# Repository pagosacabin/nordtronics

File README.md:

# Nordtronics

Code, hardware designs, and CAD models from **Nordtronics** (Pagosa Springs, CO) —
an off-grid solar, battery, and IoT practice. Custom LiFePO4 battery builds,
off-grid solar installs, and wireless sensor systems (ESP32 / LoRa / MQTT /
Home Assistant).

## Layout

- `backend/` — wildfire pipeline: Mosquitto broker, ingest worker, read-only
  FastAPI service, and the deployment guide (`DEPLOY.md`).
- `firmware/wildfire-node-v1/` — unified LoRa wildfire node/base-station
  firmware (Heltec LoRa 32 V4).
- `android/companion-v0/` — Android companion app for the wildfire network.
- `website/` — nordtronics.io site.
- `docs/` — runbooks and design docs (`docs/wildfire/` for the wildfire net).
- `firmware/cistern-monitor/` — Tank-Monitor remote cistern level monitor:
  ESP32-S3 + SX1262 LoRa TX/RX pair, ultrasonic level sensing, MQTT/Home
  Assistant integration (`cistern_unified.ino`).
- `firmware/lora-display/` — LoRa radio experiments on Heltec LoRa V3 boards,
  including display and RF-preset sketches.
- `python/ultrasonic-sensors/` — MicroPython scripts for ultrasonic distance
  sensing with OLED/LCD output.
- `hardware/battery-pcb/` — KiCad project archives for the custom main battery
  PCB (JK BMS based LiFePO4 pack), including versioned iterations.
- `hardware/busbar/` — Busbar designs for EVE 280Ah cells.
- `cad/first-project/` — Early KiCad project archives.
- `cad/robotic-arm/` — Robotic arm 3D model (STEP).

Archived `.zip` files are kept as-is, preserving the original design history.
- `installs/solar/` — Off-grid solar + storage install notes.

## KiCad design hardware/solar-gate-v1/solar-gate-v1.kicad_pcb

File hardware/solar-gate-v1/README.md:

# solar-gate-v1 — solar cold-charge gate (EDA flow test vehicle)

**TEST BOARD ONLY. Not production, not reviewed, no Gerbers, no fab output.**

This project exists to cold-test the schematic → layout → autoroute rung of the
toolchain against a real circuit. The circuit itself is the approved solar
cold-charge gate spec, but nothing here has been bench-validated and nothing
should be built from it until Stephen has reviewed both the schematic and the
layout.

## Circuit

Warm → NTC low → `VA < VTH` → comparator output pulls `GATE` low → Q1 on.
Cold / no sun → `GATE` floats to `Panel+` through Rg → Q1 off.

| Ref | Part | Package | Notes |
|-----|------|---------|-------|
| Q1  | AO3401 (P-ch MOSFET) | SOT-23 | 1=G, 2=S, 3=D |
| U1  | TLV3401 (nanopower comparator, open-drain) | **SOT-23-5** | see pinout note below |
| D1  | TL431 (2.5 V shunt reference) | SOT-23-3 | 1=K, 2=REF, 3=A (TI DBZ); REF tied to K |
| TH1 | 10k NTC B=3950, **off-board** → 2-pin JST GH 1.25 mm | — | board-edge connector |
| Rs  | 12k | 0805 | Panel+ → REF2V5 |
| R1, R2, R3 | 30k | 0805 | VA / VTH dividers |
| Rf  | 270k | 0805 | GATE → VA feedback |
| Rg  | 100k | 0805 | Panel+ → GATE pull-up |
| R4, R5 | 100k | 0805 | telemetry divider, GATE → GPIO |
| C1  | 100nF | 0805 | across D1 |
| C2  | 10nF | 0805 | VA → GND |
| J1, J2, J4 | JST GH 1.25 mm 2-pin | — | panel in / charger out / telemetry out |

Nets: `Panel+`, `GND`, `REF2V5`, `VA`, `VTH`, `GATE`, `CHG+`, `TELEM`.

### D1 reference — TL431 (task 0043)

The first pass drew D1 as a TLV431, whose `VREF` is 1.24 V, so the
`REF2V5`/`VTH` targets did not hold (0039 open item 1). D1 is now a **TL431**
(TI SLVS543S, DBZ SOT-23-3: **1 = K, 2 = REF, 3 = A**), with the divider values
left as computed for 2.5 V.

The board did not change. `REF` and `K` are both on `REF2V5` by design, so
D1 pad 1 (K) and pad 2 (REF) were already shorted on that net, pad 3 (A) was
already on `GND`, and the footprint is the same `Package_TO_SOT_SMD:SOT-23`.
`solar-gate-v1.kicad_pcb` is byte-identical to the 0039 tip
(`sha256 95c7c0b279688f20cd8d84435e144e05e4ca9093e4f3c9af582df41f32b13893`).
Note the pinout trap: a TLV431 in DBZ is 1=REF / 2=CATHODE / 3=ANODE, the
*opposite* of the TL431 in the same package — the two are interchangeable here
only because REF and K are tied together.

Bias current: the TL431 needs 0.4–1 mA of cathode current to regulate
(TLV431: 55–80 µA), and `Rs` = 12k from `Panel+` sets that current. The
implication is reported in the 0043 reply; no bias-network or divider change
was made.

## Board

2-layer, 40 × 30 mm, 1 oz copper, all parts on the front. Power path along the
top edge (J1 → Q1 → J2); TH1 and J4 on board edges; NTC is off-board.

Track widths (IPC-2221, external layer, 1 oz, 10 °C rise):

| Net class | Nets | Width | Rationale |
|-----------|------|-------|-----------|
| `POWER_1A` | `Panel+`, `CHG+`, `GND` | **0.80 mm** | 1 A needs 0.30 mm minimum; 0.8 mm ≈ 2.0 A capability |
| `SIGNAL_0R25` | `VA`, `VTH`, `GATE`, `REF2V5`, `TELEM` | 0.25 mm (routed at 0.20 mm, see below) | signal only |

`GND` is in the high-current class because it carries the 1 A return
(panel− → charger−).

## How it was built

Entirely through the KiCad MCP server (mixelpixx/KiCAD-MCP-Server 2.7.0) —
project/schematic creation, symbol authoring, wiring, ERC, board sync,
placement, autoroute via Freerouting 2.4.1, and DRC. No hand-edited KiCad
files, no hand-routing.

- ERC: `solar-gate-v1-erc.txt` — **0 errors, 0 warnings**
- DRC: `solar-gate-v1_drc_violations.json` — **2 errors, 0 warnings**
  (both are Freerouting fanout stubs at 0.15 mm on net `VA`, below the
  declared 0.20 mm minimum — router output, left as-is and reported)
- Autoroute: `solar-gate-v1.dsn` / `solar-gate-v1.ses`. Freerouting reported
  `0 unrouted and 0 violations`, final score 999.99; fanout escaped 39/39 SMD
  pins. 117 segments, 11 vias on the board; all 8 nets have copper.

## Open items for review

1. **Resolved in 0043 — D1 is now a TL431, a true 2.5 V reference.** With REF
   tied to K the reference node sits at 2.5 V, so R2/R3 halve it to the
   specified 1.25 V and the divider values stand. What replaces it as a live
   question is bias current: the TL431 needs 0.4–1 mA of cathode current to
   regulate where the TLV431 needed 55–80 µA, and `Rs` = 12k sets that current
   from `Panel+`. Numbers are in the 0043 reply; nothing was re-scaled.
2. **U1 pin 5 = VCC, pin 2 = GND, pin 3 = IN+, pin 4 = IN−** (TLV3401 has no
   SC-70-5 package; the spec's SC-70-5 call was corrected to SOT-23-5).
3. **J4 (telemetry out) is an addition** — the spec listed only panel in,
   GND and charger out, but `TELEM` has to leave the board somehow.
4. `SIGNAL_0R25` never took effect: those five nets fell back to the board's
   `Default` class and were routed at 0.20 mm (still fine for signals).
5. Two DRC `track_width` errors are unresolved router output, deliberately not
   hand-fixed.

## Environment notes

The Flatpak KiCad 10 sandbox has its own `/usr`, so host library paths are
invisible to it:

- `fp-lib-table` in this directory points at the Flatpak **KiCad 10 footprint
  runtime** (`/var/lib/flatpak/runtime/.../footprints/...`), a host path both
  the host `pcbnew` backend and the sandboxed `kicad-cli` 10 can read. Pointing
  at `/usr/share/kicad/footprints` instead makes ERC/DRC report every footprint
  library as "not enabled in the current configuration".
- `sym-lib-table` now points the project library at
  `${KIPRJMOD}/solar-gate-v1.kicad_sym` instead of an absolute checkout path.
  The old absolute path broke ERC the moment the project was opened from any
  other checkout or worktree: `kicad-cli` reported `The symbol library
  'solar-gate-v1' was not found at '<abs path>'` for every project symbol.
- The MCP server's symbol loader needs `KICAD_SYMBOL_DIR` set to the same
  runtime's `symbols/` directory, or the schematic's cached symbols are written
  from the host KiCad 9 libraries and every symbol then mismatches the KiCad 10
  library the ERC engine reads.

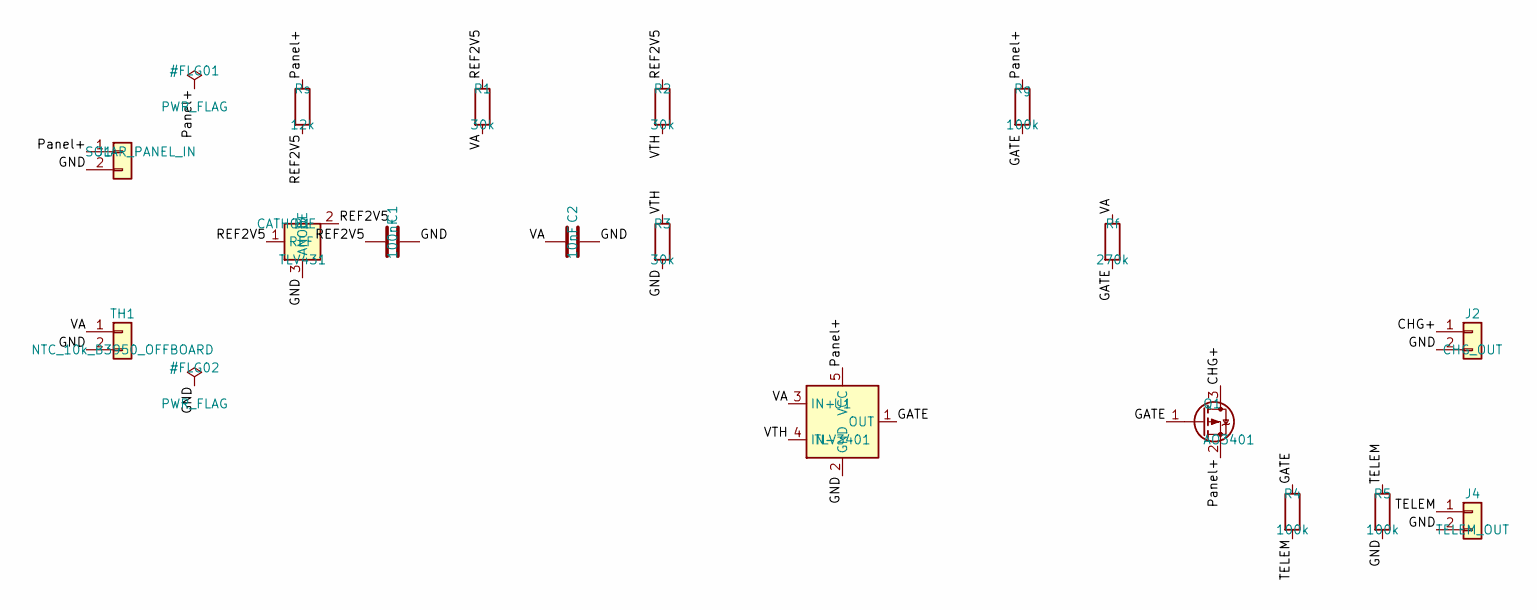
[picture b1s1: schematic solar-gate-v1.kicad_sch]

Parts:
C1: 100nF; C_0805_2012Metric
C2: 10nF; C_0805_2012Metric
D1: TLV431; SOT-23
J1: SOLAR_PANEL_IN; JST_GH_BM02B-GHS-TBT_1x02-1MP_P1.25mm_Vertical
J2: CHG_OUT; JST_GH_BM02B-GHS-TBT_1x02-1MP_P1.25mm_Vertical
J4: TELEM_OUT; JST_GH_BM02B-GHS-TBT_1x02-1MP_P1.25mm_Vertical
Q1: AO3401; SOT-23
R1, R2, R3: 30k; R_0805_2012Metric
R4, R5: 100k; R_0805_2012Metric
Rf: 270k; R_0805_2012Metric
Rg: 100k; R_0805_2012Metric
Rs: 12k; R_0805_2012Metric
TH1: NTC_10k_B3950_OFFBOARD; JST_GH_BM02B-GHS-TBT_1x02-1MP_P1.25mm_Vertical
U1: TLV3401; SOT-23-5

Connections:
CHG+: J2.1, Q1.3 (D)
GATE: Q1.1 (G), R4.1, Rf.2, Rg.2, U1.1 (OUT)
GND: C1.2, C2.2, D1.3 (ANODE), J1.2, J2.2, J4.2, R3.2, R5.2, TH1.2, U1.2 (GND)
Panel+: J1.1, Q1.2 (S), Rg.1, Rs.1, U1.5 (VCC)
REF2V5: C1.1, D1.1 (REF), D1.2 (CATHODE), R1.1, R2.1, Rs.2
TELEM: J4.1, R4.2, R5.1
VA: C2.1, R1.2, Rf.1, TH1.1, U1.3 (IN+)
VTH: R2.2, R3.1, U1.4 (IN-)

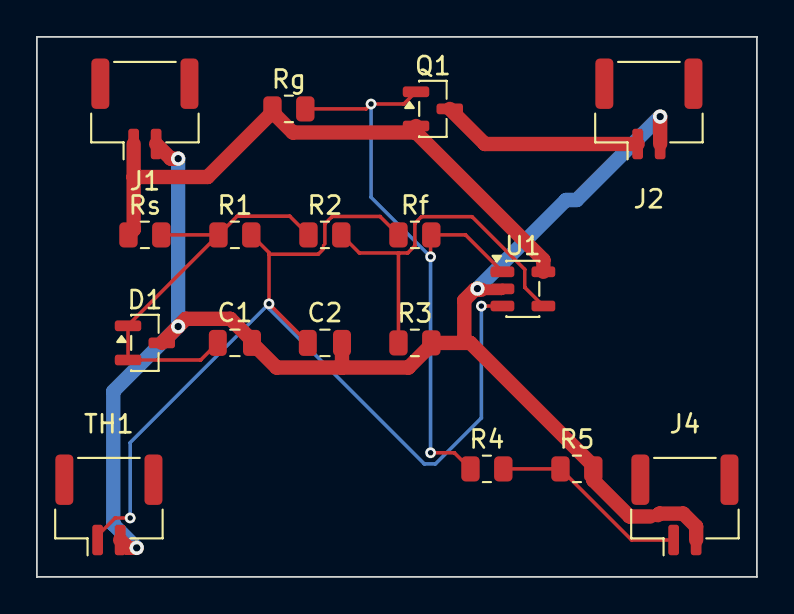
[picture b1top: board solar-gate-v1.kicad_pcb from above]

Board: 2 copper layers, 40.0 x 30.0 mm, 17 parts (0 on the bottom side), 8 nets.

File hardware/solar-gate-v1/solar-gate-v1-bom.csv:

value,footprint,quantity,references
SOLAR_PANEL_IN,Connector_JST:JST_GH_BM02B-GHS-TBT_1x02-1MP_P1.25mm_Vertical,1,['J1']
100k,Resistor_SMD:R_0805_2012Metric,3,"['Rg', 'R4', 'R5']"
CHG_OUT,Connector_JST:JST_GH_BM02B-GHS-TBT_1x02-1MP_P1.25mm_Vertical,1,['J2']
12k,Resistor_SMD:R_0805_2012Metric,1,['Rs']
NTC_10k_B3950_OFFBOARD,Connector_JST:JST_GH_BM02B-GHS-TBT_1x02-1MP_P1.25mm_Vertical,1,['TH1']
TLV431,Package_TO_SOT_SMD:SOT-23,1,['D1']
AO3401,Package_TO_SOT_SMD:SOT-23,1,['Q1']
TLV3401,Package_TO_SOT_SMD:SOT-23-5,1,['U1']
270k,Resistor_SMD:R_0805_2012Metric,1,['Rf']
30k,Resistor_SMD:R_0805_2012Metric,3,"['R3', 'R2', 'R1']"
100nF,Capacitor_SMD:C_0805_2012Metric,1,['C1']
TELEM_OUT,Connector_JST:JST_GH_BM02B-GHS-TBT_1x02-1MP_P1.25mm_Vertical,1,['J4']
10nF,Capacitor_SMD:C_0805_2012Metric,1,['C2']
